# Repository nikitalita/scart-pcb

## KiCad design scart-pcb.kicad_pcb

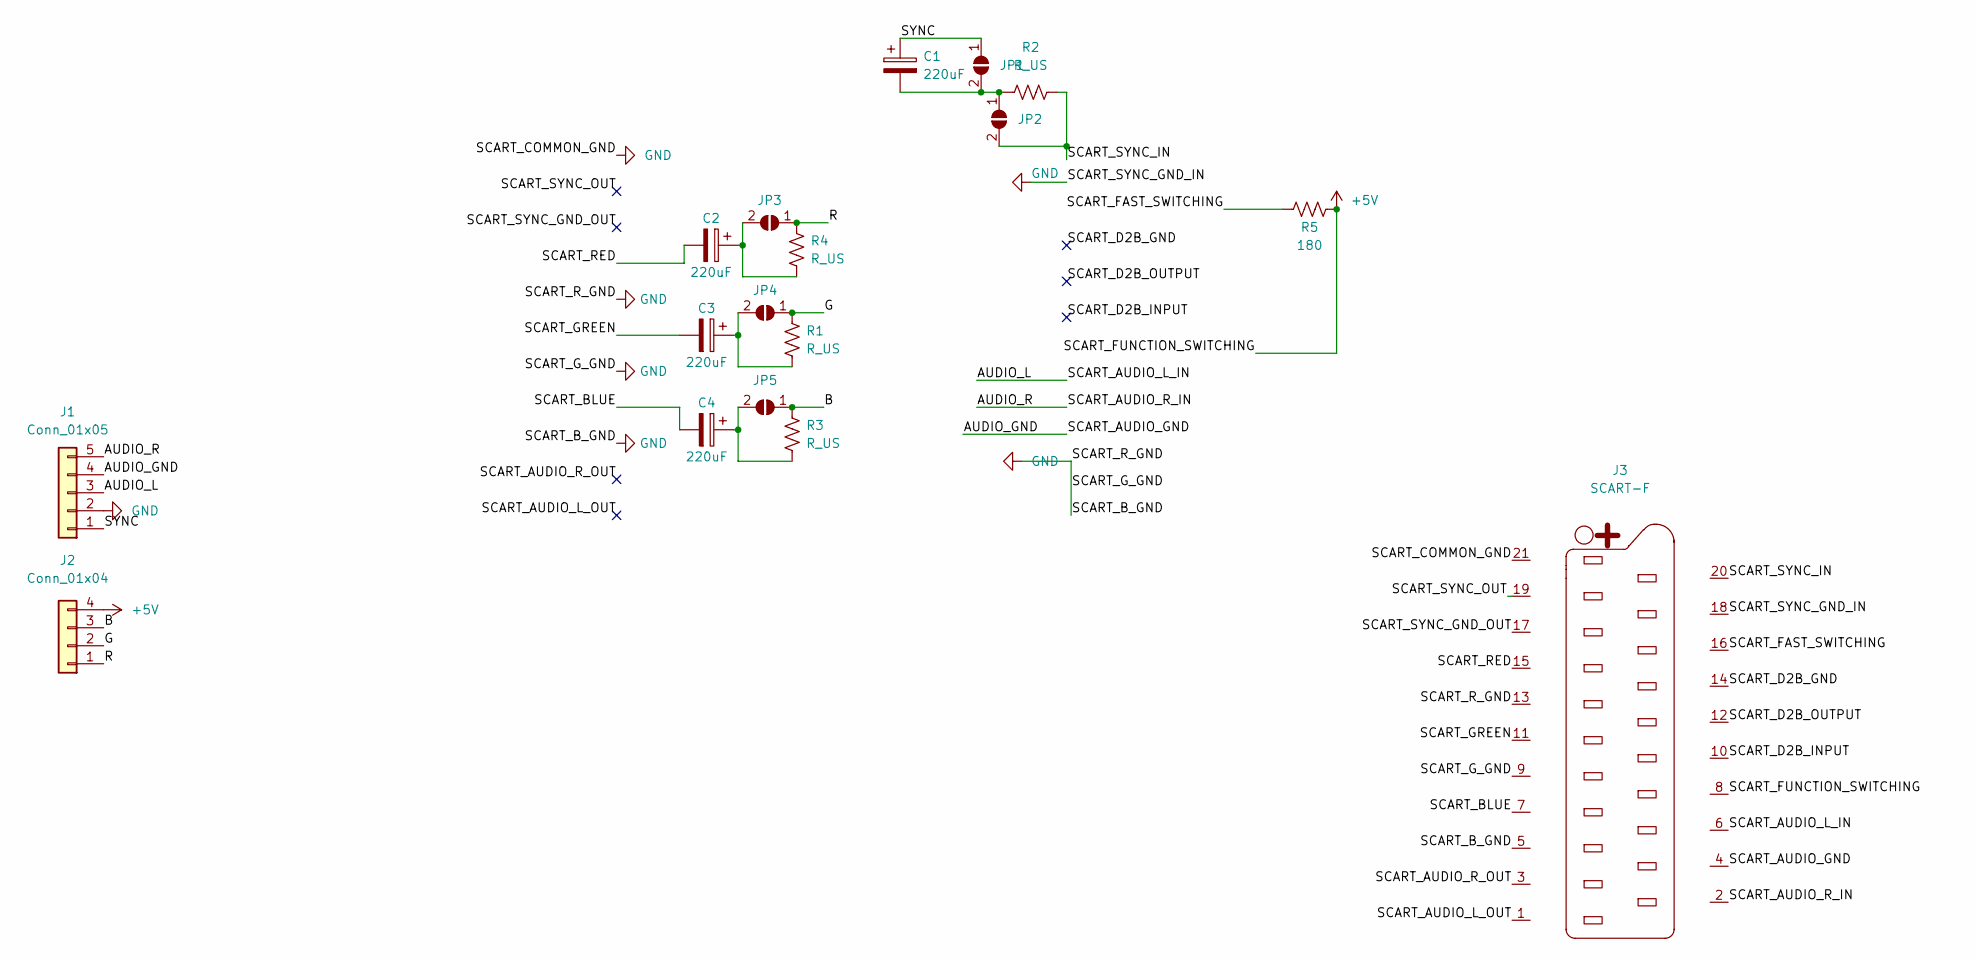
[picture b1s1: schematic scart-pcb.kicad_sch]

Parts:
C1, C2, C3, C4: 220uF; CP_Elec_6.3x5.3
J1: Conn_01x05; front_wire_pads
J2: Conn_01x04; back_wire_pads
J3: SCART-F; SCART_MALE
JP1, JP2, JP3, JP4, JP5: SolderJumper_2_Open; Triangle jumper
R1, R2, R3, R4: R_US; R_0603_1608Metric_Pad0.98x0.95mm_HandSolder
R5: 180; R_0603_1608Metric_Pad0.98x0.95mm_HandSolder

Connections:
+5V: J2.4, J3.8, R5.2
/AUDIO_GND: J1.4, J3.4
/AUDIO_L: J1.3, J3.6
/AUDIO_R: J1.5, J3.2
/B: J2.3, JP5.1 (A), R3.1
/G: J2.2, JP4.1 (A), R1.1
/R: J2.1, JP3.1 (A), R4.1
/SCART_AUDIO_L_OUT: J3.1
/SCART_AUDIO_R_OUT: J3.3
/SCART_BLUE: C4.2, J3.7
/SCART_D2B_GND: J3.14
/SCART_D2B_INPUT: J3.10
/SCART_D2B_OUTPUT: J3.12
/SCART_FAST_SWITCHING: J3.16, R5.1
/SCART_GREEN: C3.2, J3.11
/SCART_RED: C2.2, J3.15
/SCART_SYNC_GND_OUT: J3.17
/SCART_SYNC_IN: J3.20, JP2.2 (B), R2.2
/SCART_SYNC_OUT: J3.19
/SYNC: C1.1, J1.1, JP1.1 (A)
GND: J1.2, J3.5, J3.9, J3.13, J3.18, J3.21
unnamed: C1.2, JP1.2 (B), JP2.1 (A), R2.1
unnamed: C2.1, JP3.2 (B), R4.2
unnamed: C3.1, JP4.2 (B), R1.2
unnamed: C4.1, JP5.2 (B), R3.2

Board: 2 copper layers, 18 parts (9 on the bottom side), 18 nets, no tracks yet.

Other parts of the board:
C**: 6TPE220MZB
